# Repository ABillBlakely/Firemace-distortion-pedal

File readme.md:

# Firemace

## The Project:

Distortion pedals are one of the most basic and most used types of guitar effects pedal, and this project serves as a good introduction into the world of guitar effects building.
The Firemace is based on [Robin Tomtlunds Red Fuzz](http://www.generalguitargadgets.com/effects-projects/distortion/red-fuzz/) design.
This project is designed to be an easy to build kit with possibility of modification and customization.

## The Objective:

Learn the inner workings of distortion pedals, and the common techniques involved in building most guitar effect pedals.
Build your skills in circuit assembly and circuit analysis, and use your creativity to personalize the pedal.
The project builds skills including op-amp and transistor analysis, soldering, enclosure building.
Along the way you will get an introduction to PCB design, electronics prototyping, electronic components, common circuit blocks, time and frequency domain analysis.

## This repository

While you are here, check out the [schematic](firemace-schematic.pdf), the potential [modifications](modifications/), or view the PCB [front](firemace-pcb-front.png) and [back](firemace-pcb-back.png). You can also get the [bill of materials](firemace-BOM.xlsx).

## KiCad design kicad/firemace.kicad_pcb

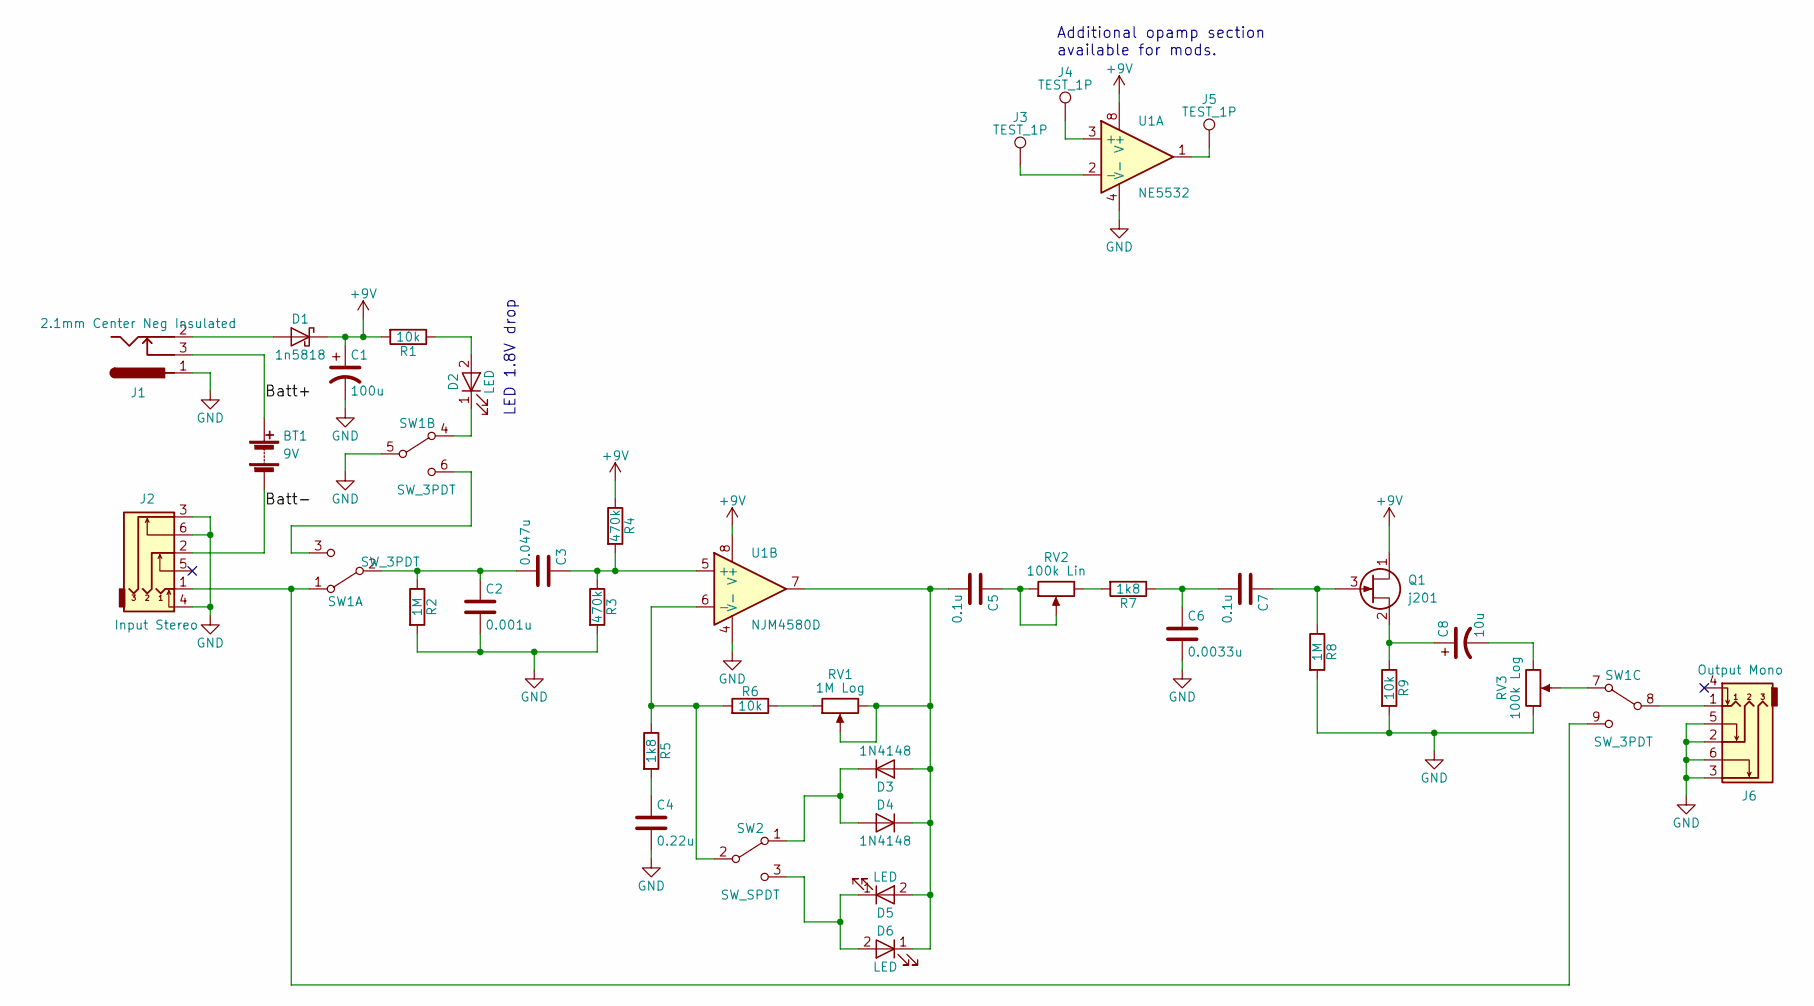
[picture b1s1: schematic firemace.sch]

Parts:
BT1: 9V; Pin_Header_Straight_1x02_Pitch2.54mm
C1: 100u; CP_Radial_D5.0mm_P2.50mm
C2: 0.001u; C_Disc_D6.0mm_W2.5mm_P5.00mm
C3: 0.047u; C_Disc_D7.5mm_W4.4mm_P5.00mm
C4: 0.22u; C_Disc_D7.5mm_W4.4mm_P5.00mm
C5, C7: 0.1u; C_Disc_D7.5mm_W4.4mm_P5.00mm
C6: 0.0033u; C_Disc_D5.0mm_W2.5mm_P5.00mm
C8: 10u; CP_Radial_D5.0mm_P2.50mm
D1: 1n5818; D_DO-41_SOD81_P10.16mm_Horizontal
D2: LED; LED_D5.0mm
D3, D4: 1N4148; D_DO-35_SOD27_P7.62mm_Horizontal
D5, D6: LED; LED_D3.0mm
J1: 2.1mm Center Neg Insulated; Pin_Header_Straight_1x03_Pitch2.54mm
J2: Input Stereo; Pin_Header_Straight_1x03_Pitch2.54mm
J3, J4, J5: TEST_1P; Pin_Header_Straight_1x01_Pitch2.54mm
J6: Output Mono; Pin_Header_Straight_1x02_Pitch2.54mm
Q1: j201; TO-92_Inline_Wide
R1, R6, R9: 10k; R_Axial_DIN0207_L6.3mm_D2.5mm_P10.16mm_Horizontal
R2, R8: 1M; R_Axial_DIN0207_L6.3mm_D2.5mm_P10.16mm_Horizontal
R3, R4: 470k; R_Axial_DIN0207_L6.3mm_D2.5mm_P10.16mm_Horizontal
R5, R7: 1k8; R_Axial_DIN0207_L6.3mm_D2.5mm_P10.16mm_Horizontal
RV1: 1M Log; pot_16mm_long_lead
RV2: 100k Lin; pot_16mm_long_lead
RV3: 100k Log; pot_16mm_long_lead
SW1: SW_3PDT; 3PDT_Solder_Lugs
SW2: SW_SPDT; Pin_Header_Straight_1x03_Pitch2.54mm
U1: NJM4580D; DIP-8_W7.62mm_Socket_LongPads

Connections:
+9V: C1.1, D1.1 (K), Q1.1 (D), R1.2, R4.1, U1.8 (V+)
/Batt+: BT1.1 (+), J1.3
/Batt-: BT1.2 (-), J2.2
GND: C1.2, C2.2, C4.2, C6.2, J1.1, J2.3, J2.4, J2.6, J6.2, J6.3, J6.5, J6.6, R2.2, R3.2, R8.2, R9.2, RV3.1, SW1.5 (B), U1.4 (V-)
unnamed: C2.1, C3.2, R2.1, SW1.2 (B)
unnamed: C3.1, R3.1, R4.2, U1.5 (+)
unnamed: C4.1, R5.2
unnamed: C5.1, RV2.1, RV2.2
unnamed: C5.2, D3.2 (A), D4.1 (K), D5.2 (A), D6.1 (K), RV1.2, RV1.3, U1.7
unnamed: C6.1, C7.2, R7.1
unnamed: C7.1, Q1.3 (G), R8.1
unnamed: C8.1, Q1.2 (S), R9.1
unnamed: C8.2, RV3.3
unnamed: D1.2 (A), J1.2
unnamed: D2.1 (K), SW1.4 (A)
unnamed: D2.2 (A), R1.1
unnamed: D3.1 (K), D4.2 (A), SW2.1 (A)
unnamed: D5.1 (K), D6.2 (A), SW2.3 (C)
unnamed: J2.1, SW1.1 (A), SW1.9 (C)
unnamed 19: J3.1, U1.2 (-); also elsewhere on the board
unnamed 20: J4.1, U1.3 (+); also elsewhere on the board
unnamed 21: J5.1, U1.1; also elsewhere on the board
unnamed: J6.1, SW1.8 (B)
unnamed: R5.1, R6.2, SW2.2 (B), U1.6 (-)
unnamed: R6.1, RV1.1
unnamed: R7.2, RV2.3
unnamed: RV3.2, SW1.7 (A)
unnamed: SW1.3 (C), SW1.6 (C)

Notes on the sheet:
Additional opamp section available for mods.
LED 1.8V drop

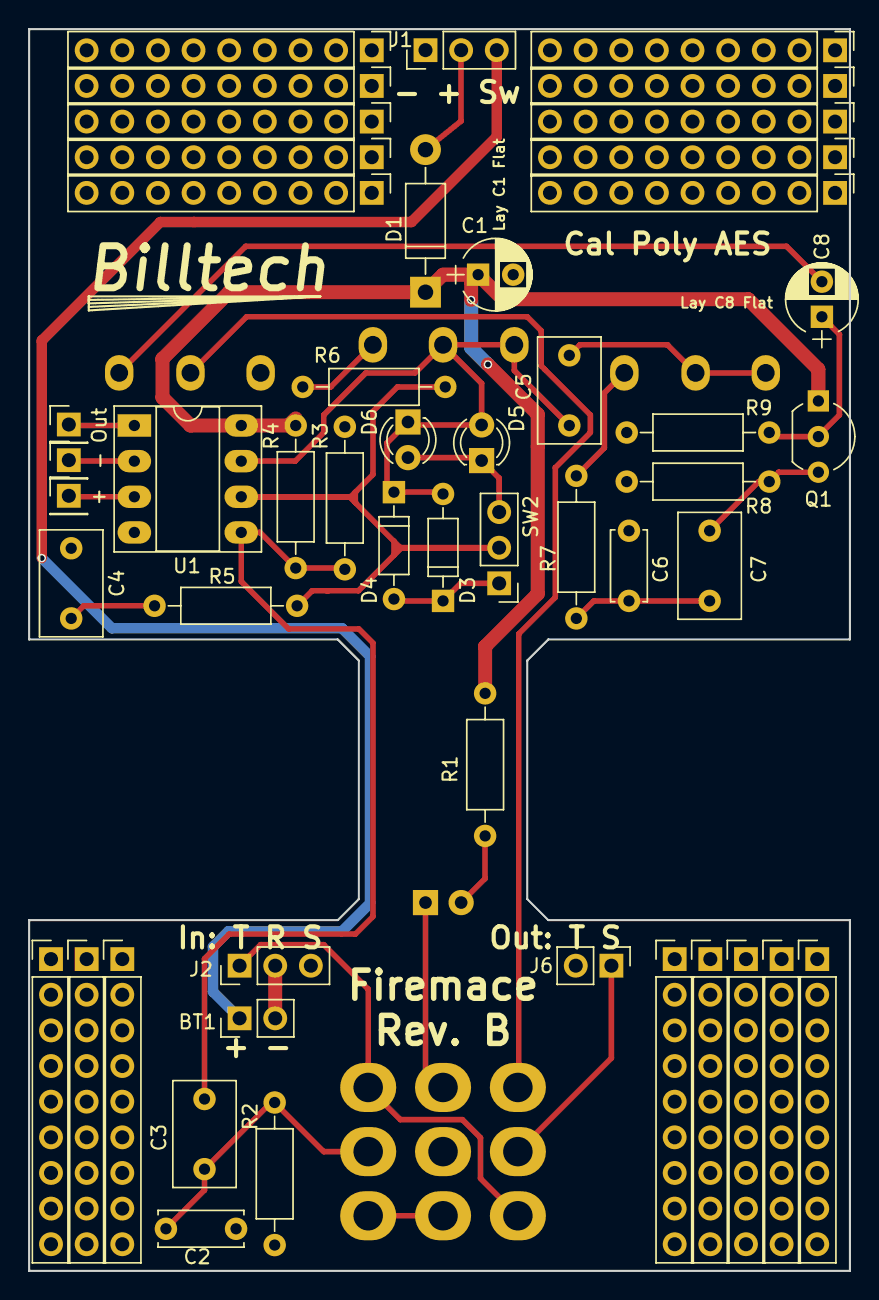
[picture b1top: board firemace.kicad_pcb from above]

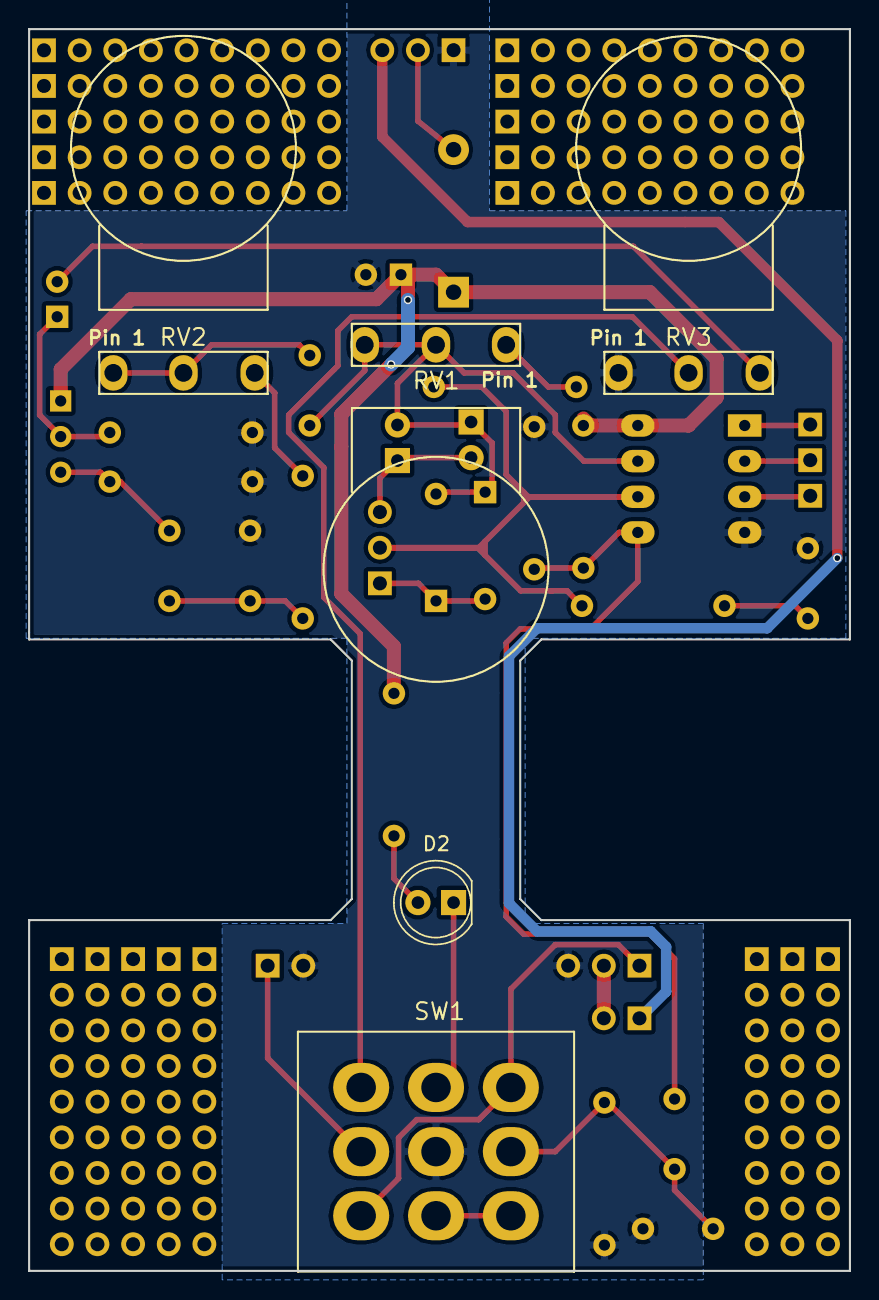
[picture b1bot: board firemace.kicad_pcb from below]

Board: 2 copper layers, 58.5 x 88.5 mm, 37 parts (5 on the bottom side), 28 nets.

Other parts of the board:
+: TEST_1P; Pin_Header_Straight_1x01_Pitch2.54mm
-: TEST_1P; Pin_Header_Straight_1x01_Pitch2.54mm
Out: TEST_1P; Pin_Header_Straight_1x01_Pitch2.54mm

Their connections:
unnamed 19: -.1; also elsewhere on the board
unnamed 20: +.1; also elsewhere on the board
unnamed 21: Out.1; also elsewhere on the board

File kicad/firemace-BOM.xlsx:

Supplier | Reference | Product | Price | Quantity | Total
SmallBear | C6 | Polyester Film Capacitors 0.0033uf : Topmay TMC05 | 0.25 | 1 | 0.25
SmallBear | C4 | Polyester Film Capacitors 0.22uf : Topmay TMC05 | 0.25 | 1 | 0.25
SmallBear | C3 | Polyester Film Capacitors 0.047uf : Topmay TMC05 | 0.25 | 1 | 0.25
SmallBear | C2 | Polyester Film Capacitors 0.001uf : Topmay TMC05 | 0.25 | 1 | 0.25
SmallBear | C5 | Polyester Film Capacitors 0.1uf : Topmay TMC05 | 0.25 | 2 | 0.5
SmallBear | C7 | Electrolytic Capacitors 10uF | 0.25 | 1 | 0.25
SmallBear | C1 | Electrolytic Capacitors 100uF | 0.35 | 1 | 0.35
SmallBear | D5 D6 | 3mm LED - Red | 0.25 | 2 | 0.5
SmallBear | D2 | 5mm LED - Red | 0.5 | 1 | 0.5
SmallBear | D1 | 1N5818 (Schottky Diode) | 0.15 | 1 | 0.15
SmallBear | D3 D4 | 1N4148 Small Signal Diode | 0.15 | 2 | 0.3
BLMS | J1 | 2.1mm DC Power Jack Solder Lug External Nut | 0.55000000000000004 | 1 | 0.55000000000000004
SmallBear | J2 | Stereo Open frame Jack Electronics | 1.25 | 1 | 1.25 | Slightly cheaper at BLMS, but out of stock
SmallBear | J6 | Mono Open frame Jack Electronics | 1.1499999999999999 | 1 | 1.1499999999999999 | Slightly cheaper at BLMS, but out of stock
BLMS | SW2 | SPDT On-On Solder Lug Toggle Switch | 0.74 | 1 | 0.74
BLMS | SW1 | 3PDT Stomp solder lug | 2.1800000000000002 | 1 | 2.1800000000000002
SmallBear | R5 R7 | Bag of 100 - 1/4 Watt Metal Film Resistor - 1.8K ohms | 2 | 0.02 | 0.04
SmallBear | R1 R6 R9 | Bag of 200 - 1/4 Watt Metal Film Resistor - 10K ohms | 3.95 | 1.4999999999999999E-2 | 5.9249999999999997E-2
SmallBear | R3 R4 | Bag of 100 - 1/4 Watt Metal Film Resistor - 470K ohms | 2 | 0.02 | 0.04
SmallBear | R2 R8 | Bag of 200 - 1/4 Watt Metal Film Resistor - 1.0M ohms | 3.95 | 0.01 | 3.95E-2
SmallBear | RV2 | Alpha Potentiometer Linear (B)16mm Single Gang PCB Mount 90Â° Long Pin - B100K | 1.25 | 1 | 1.25
SmallBear | RV3 | Alpha Potentiometer Logarithmic (A)16mm Single Gang PCB Mount 90Â° Long Pin - A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 | 1.25 | 1 | 1.25
SmallBear | RV1 | Alpha Potentiometer Logarithmic (A)16mm Single Gang PCB Mount 90Â° Long Pin - A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 | 1.25 | 1 | 1.25
SmallBear | U1 | NJM4580D (IC) | 0.55000000000000004 | 1 | 0.55000000000000004
SmallBear | Q1 | J201 N-Channel JFET General Purpose Amplifier Transistor | 0.59 | 1 | 0.59
SmallBear | Enclosure | 125B(4.77 x 2.6 x 1.39) Painted | 6.25 | 1 | 6.25
SmallBear | Knobs | Large Fluted MXR Style Colored | 0.8 | 3 | 2.4000000000000004
SmallBear | DIP-8 Socket | DIP-8 Socket | 0.64 | 1 | 0.64
SmallBear | SIP socket | SIP20 Socket Snap-off | 2.5 | 0.15 | 0.375
BLMS | LED Bezel | Bag of 5 5mm LED Bezel Black | 1.25 | 0.2 | 0.25
SmallBear | Batt Snap | T-style 9V | 0.35 | 1 | 0.35
SmallBera | Batt | 9V Battery | 2.15 | 1 | 2.15
Shipping Small bear | Shipping | Fedex for order of 10 | 30 | 0.1 | 3
BLMS | Shipping |  | 6.95 | 0.1 | 0.69500000000000006
SeeedStudio | PCB | Set of 20 incl. shipping | 31.42 | 0.05 | 1.5710000000000002
 |  |  |  | Total | 32.169750000000001
 |  |  |  | Plus tax | 34.823754375
 |  |  |  | Plus FUA | 41.78850525

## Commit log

2018-01-14 PCB design prototype for AES pedal kit.
2018-02-09 Project Rev. B
2018-02-10 minor changes to match available supply. Add new BOM.
2018-02-10 Create basic verison of led bezel.
2018-02-10 Rename to firemace, add most of the missing parts from 3d model.
2018-02-10 Fix image link
2018-02-15 Fix naming scheme to reflect use of version control.
2018-02-16 Add first draft modifications section.
2018-02-17 Fix link to image.
2018-02-17 Move BOM to project root.
2018-02-17 Rename modifications.md to readme.md
2018-02-17 add modifications readme.md
2018-02-17 Add pcb images, improve readme
2018-02-17 Place text above image.
2018-02-17 Fix typo
2018-02-23 readme.md
2018-04-12 Correct a couple of typos.
